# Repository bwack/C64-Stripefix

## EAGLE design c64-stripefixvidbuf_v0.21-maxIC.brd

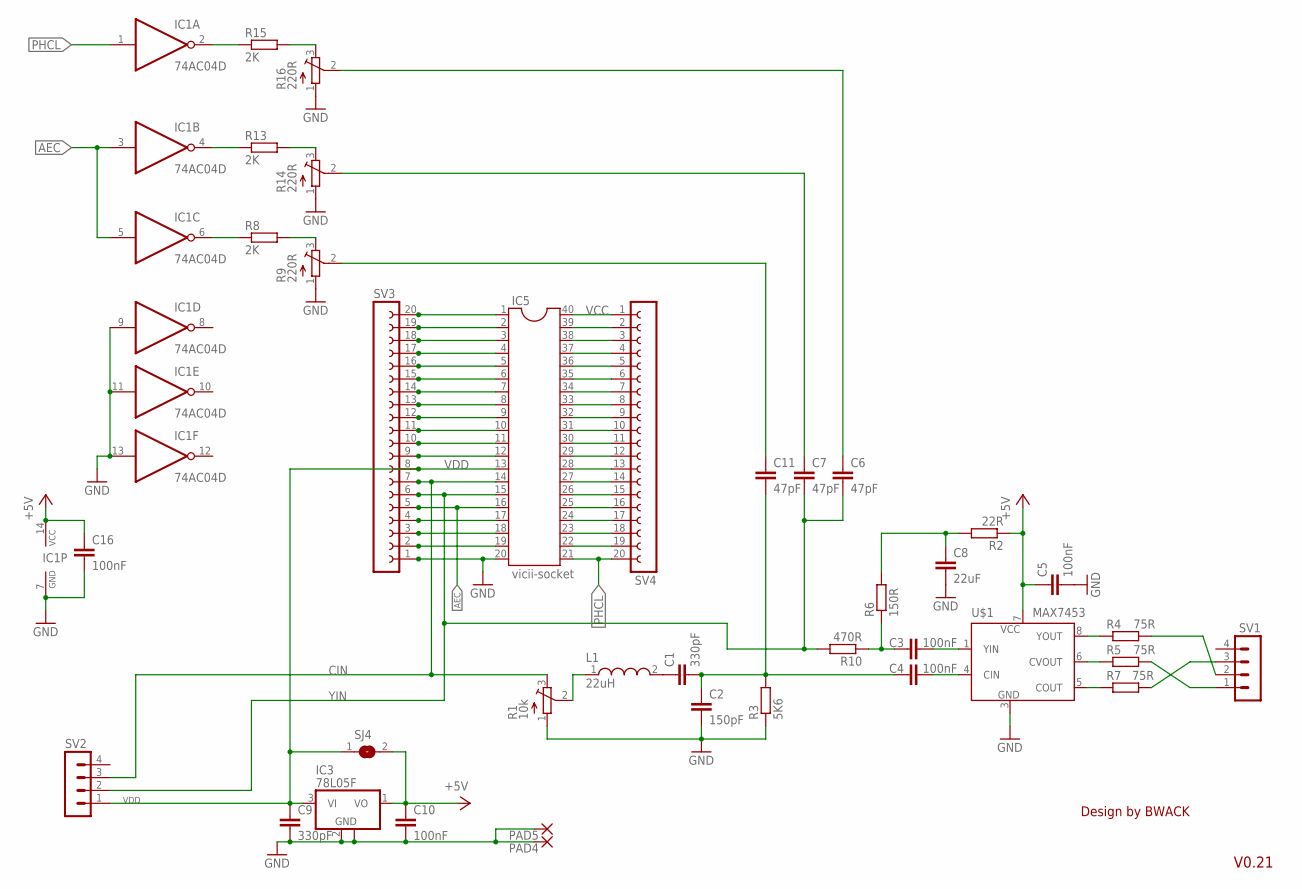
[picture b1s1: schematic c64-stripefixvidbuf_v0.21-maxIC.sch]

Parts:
C1, C9: 330pF; C0603
C2: 150pF; C0603
C3, C4, C5, C10, C16: 100nF; C0603
C6, C7, C11: 47pF; C0603
C8: 22uF; C1206K
IC1: 74AC04D; SO14
IC3: 78L05F; SOT89
IC5: vicii-socket; DIL40SPECIAL
L1: 22uH; WE-KI_0805_B
PAD4, PAD5: 2,15/1,0
R1: 10k; TC33
R2: 22R; R0603
R3: 5K6; R0603
R4, R5, R7: 75R; R0603
R6: 150R; R0603
R8, R13, R15: 2K; R0603
R9, R14, R16: 220R; TC33
R10: 470R; R0603
SJ4: SJ
SV1, SV2: MA04-1S
SV3, SV4: FE20-1; FE20
U$1: MAX7453; SO08

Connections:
+5V: C5.1, C10.1, C16.1, IC1.14 (VCC), IC3.1 (VO), R2.1, SJ4.2, U$1.7 (V+)
AEC: IC1.3 (I), IC1.5 (I), IC5.16, SV3.5
CHROMA_OUT: R7.2, SV1.3
CIN: IC5.14, R1.3 (E), SV2.3, SV3.7
COMPOSITE: R5.2, SV1.1
GND: C2.2, C5.2, C8.2, C9.2, C10.2, C16.2, IC1.7 (GND), IC1.9 (I), IC1.11 (I), IC1.13 (I), IC3.2 (GND), IC3.2@1 (GND), IC5.20, PAD4.1, PAD5.1, R1.1 (A), R3.1, R9.1 (A), R14.1 (A), R16.1 (A), SV3.1, U$1.3 (V-)
LUMA_OUT: R4.2, SV1.2
unnamed: R4.1, U$1.8 (YOUT)
unnamed: C1.2, C2.1, C4.1, C11.2, R3.2
unnamed: IC5.22, SV4.19
unnamed: IC5.23, SV4.18
unnamed: IC1.4 (O), R13.1
unnamed: R8.2, R9.3 (E)
unnamed: R5.1, U$1.6 (CVOUT)
unnamed: C1.1, L1.2
unnamed: IC5.24, SV4.17
unnamed: R13.2, R14.3 (E)
unnamed: R7.1, U$1.5 (COUT)
unnamed: C6.1, R16.2 (S)
unnamed: C7.1, R14.2 (S)
unnamed: C3.2, U$1.1 (YIN)
unnamed: IC5.25, SV4.16
unnamed: C4.2, U$1.4 (CIN)
unnamed: R15.2, R16.3 (E)
unnamed: IC1.6 (O), R8.1
unnamed: IC5.26, SV4.15
unnamed: C8.1, R2.2, R6.2
unnamed: L1.1, R1.2 (S)
unnamed: C11.1, R9.2 (S)
unnamed: IC1.2 (O), R15.1
unnamed: IC5.27, SV4.14
unnamed: IC5.28, SV4.13
unnamed: IC5.29, SV4.12
unnamed: IC5.30, SV4.11
unnamed: IC5.31, SV4.10
unnamed: IC5.32, SV4.9
unnamed: IC5.33, SV4.8
unnamed: IC5.34, SV4.7
unnamed: IC5.35, SV4.6
unnamed: IC5.36, SV4.5
unnamed: IC5.37, SV4.4
unnamed: IC5.38, SV4.3
unnamed: IC5.39, SV4.2
unnamed: C3.1, R6.1, R10.1
unnamed: IC5.19, SV3.2
unnamed: IC5.18, SV3.3
unnamed: IC5.17, SV3.4
unnamed: IC5.12, SV3.9
unnamed: IC5.11, SV3.10
unnamed: IC5.10, SV3.11
unnamed: IC5.9, SV3.12
unnamed: IC5.8, SV3.13
unnamed: IC5.7, SV3.14
unnamed: IC5.6, SV3.15
unnamed: IC5.5, SV3.16
unnamed: IC5.4, SV3.17
unnamed: IC5.3, SV3.18
unnamed: IC5.2, SV3.19
unnamed: IC5.1, SV3.20
PHCL: IC1.1 (I), IC5.21, SV4.20
VCC: IC5.40, SV4.1
VDD: C9.1, IC3.3 (VI), IC5.13, SJ4.1, SV2.1, SV3.8
YIN: C6.2, C7.2, IC5.15, R10.2, SV2.2, SV3.6

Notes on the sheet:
Design by BWACK
V0.21

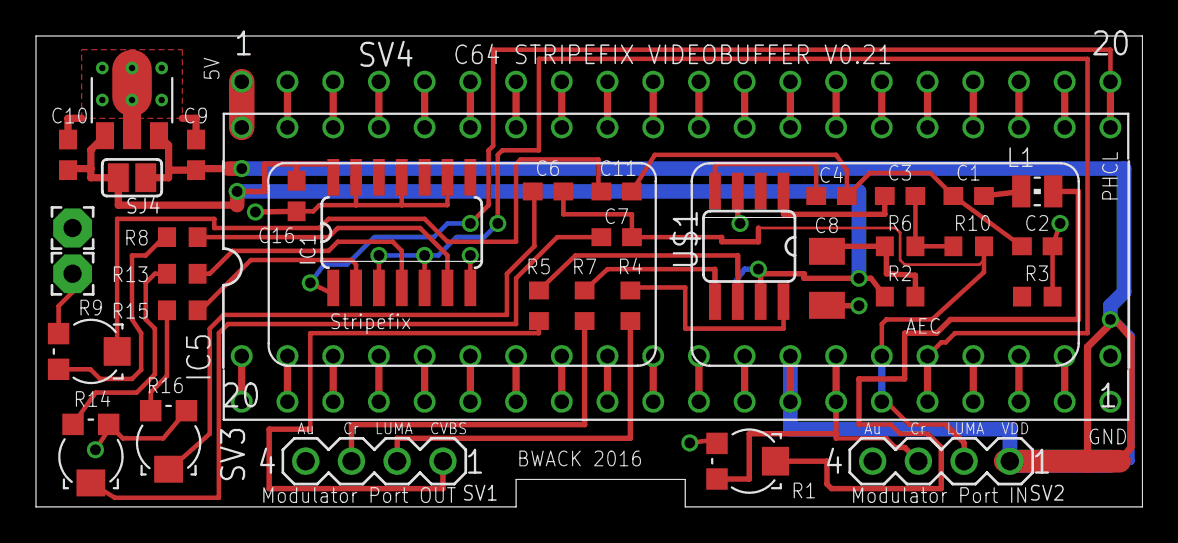
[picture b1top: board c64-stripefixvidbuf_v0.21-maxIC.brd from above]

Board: 2 copper layers, 61.5 x 26.2 mm, 38 parts (1 on the bottom side), 63 nets.

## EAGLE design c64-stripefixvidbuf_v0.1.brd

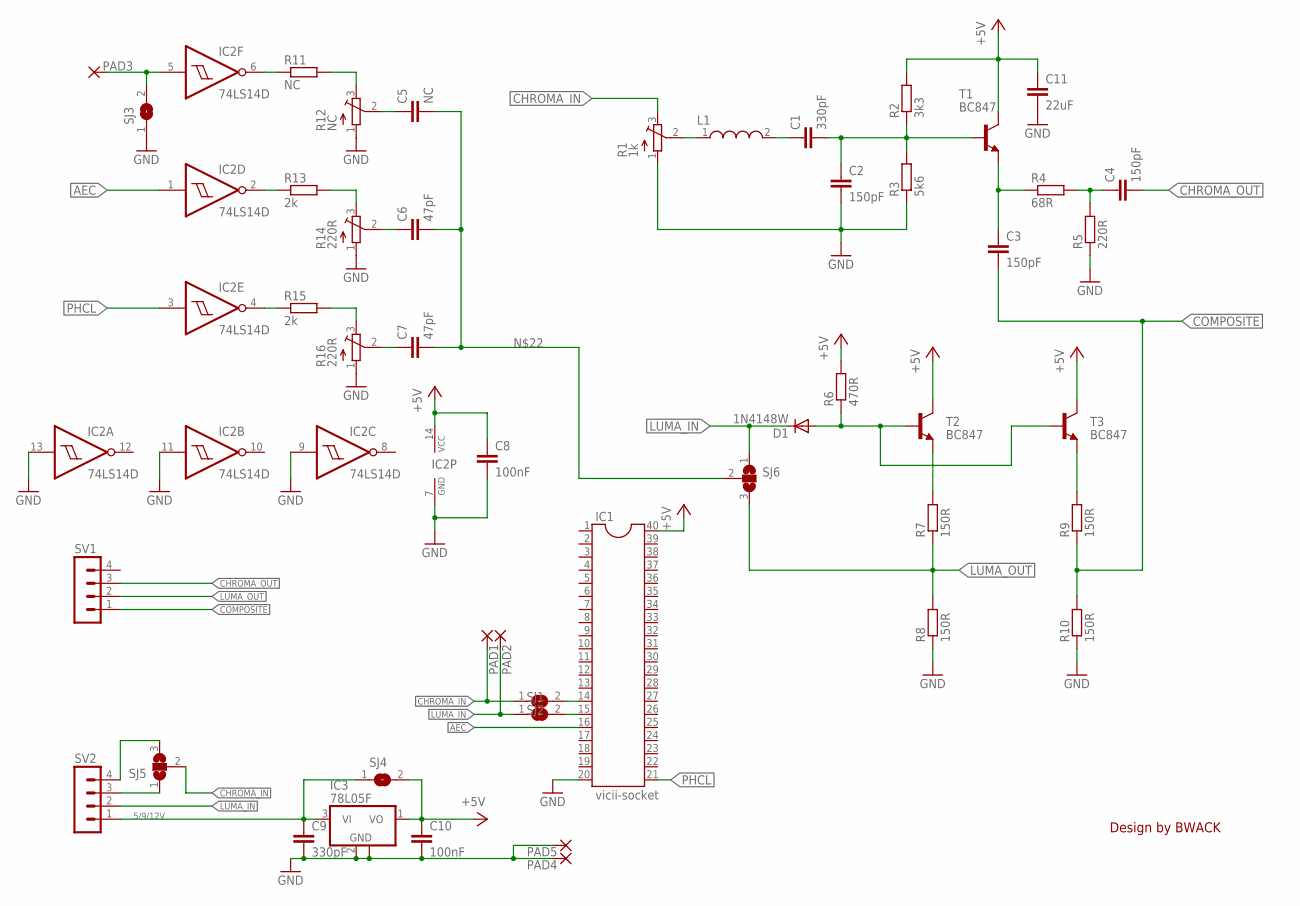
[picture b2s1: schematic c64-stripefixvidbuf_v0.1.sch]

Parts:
C1, C9: 330pF; C0603
C2, C3, C4: 150pF; C0603
C5: NC; C0603
C6, C7: 47pF; C0603
C8, C10: 100nF; C0603
C11: 22uF; C1206
D1: 1N4148W; SOD123
IC1: vicii-socket; DIL40SPECIAL
IC2: 74LS14D; SO14
IC3: 78L05F; SOT89
L1: WE-KIHQ_0805; WE-KI_0805_B
PAD1, PAD2, PAD3: SMD2; SMD1,27-2,54
PAD4, PAD5: 2,15/1,0
R1: 1k; TC33
R2: 3k3; R0603
R3: 5k6; R0603
R4: 68R; R0603
R5: 220R; R0603
R6: 470R; R0603
R7, R8, R9, R10: 150R; R0603
R11: NC; R0603
R12: NC; TC33
R13, R15: 2k; R0603
R14, R16: 220R; TC33
SJ1, SJ2, SJ3, SJ4: SJ
SJ5, SJ6: SJ2W; SJ_2
SV1, SV2: MA04-1
T1, T2, T3: BC847; SOT23

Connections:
5/9/12V: C9.1, IC3.3 (VI), SJ4.1, SV2.1
+5V: C8.1, C10.1, C11.1, IC1.40, IC2.14 (VCC), IC3.1 (VO), R2.2, R6.2, SJ4.2, T1.3 (C), T2.3 (C), T3.3 (C)
AEC: IC1.16, IC2.1 (I)
CHROMA_IN: PAD1.1, R1.3 (E), SJ1.1, SJ5.2
CHROMA_OUT: C4.2, SV1.3
COMPOSITE: C3.2, R9.1, R10.2, SV1.1
GND: C2.2, C8.2, C9.2, C10.2, C11.2, IC1.20, IC2.7 (GND), IC2.9 (I), IC2.11 (I), IC2.13 (I), IC3.2 (GND), IC3.2@1 (GND), PAD4.1, PAD5.1, R1.1 (A), R3.1, R5.1, R8.1, R10.1, R12.1 (A), R14.1 (A), R16.1 (A), SJ3.1
LUMA_IN: D1.C, PAD2.1, SJ2.1, SJ6.1, SV2.2
LUMA_OUT: R7.1, R8.2, SJ6.3, SV1.2
unnamed: R9.2, T3.2 (E)
unnamed: D1.A, R6.1, T2.1 (B), T3.1 (B)
unnamed: IC1.14, SJ1.2
unnamed: IC1.15, SJ2.2
unnamed: SJ5.1, SV2.3
unnamed: SJ5.3, SV2.4
unnamed: IC2.2 (O), R13.1
unnamed: C1.1, L1.2
unnamed: C1.2, C2.1, R2.1, R3.2, T1.1 (B)
unnamed: R13.2, R14.3 (E)
unnamed: C3.1, R4.1, T1.2 (E)
unnamed: C6.1, R14.2 (S)
unnamed: C7.1, R16.2 (S)
unnamed: R7.2, T2.2 (E)
unnamed: IC2.4 (O), R15.1
unnamed: L1.1, R1.2 (S)
unnamed: R15.2, R16.3 (E)
unnamed: IC2.6 (O), R11.1
unnamed: R11.2, R12.3 (E)
unnamed: C5.1, R12.2 (S)
unnamed: IC2.5 (I), PAD3.1, SJ3.2
unnamed: C5.2, C6.2, C7.2, SJ6.2
PHCL: IC1.21, IC2.3 (I)
QEQWEQW: C4.1, R4.2, R5.2

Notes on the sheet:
Design by BWACK

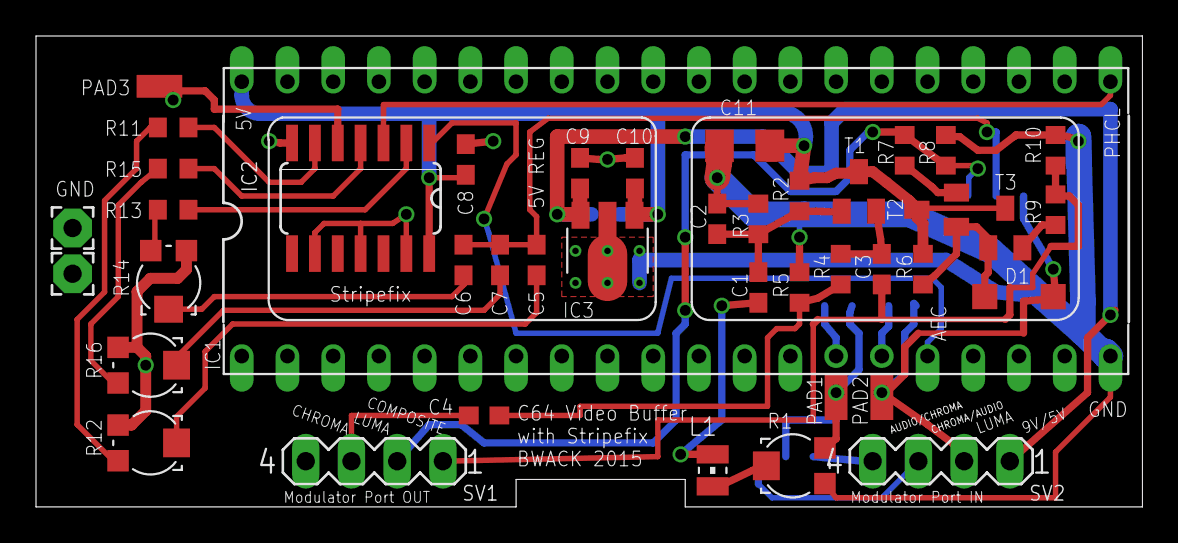
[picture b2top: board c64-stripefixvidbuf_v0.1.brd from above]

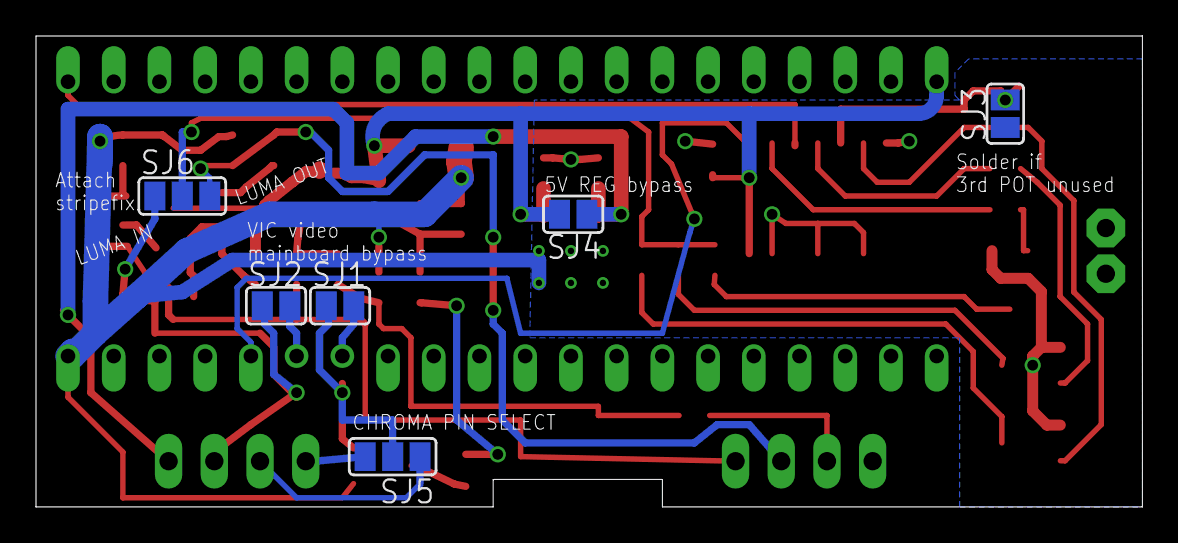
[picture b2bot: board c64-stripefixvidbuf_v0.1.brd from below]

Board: 2 copper layers, 61.5 x 26.2 mm, 48 parts (6 on the bottom side), 33 nets.

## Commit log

2016-09-20 :neckbeard: Added .gitattributes & .gitignore files
2016-09-20 second commit

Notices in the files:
parts and their libraries:
Wurth_Elektronik_Passive_rev15f: Copyright: Würth Elektronik
